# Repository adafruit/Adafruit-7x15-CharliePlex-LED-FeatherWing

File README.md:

## Adafruit 7x15 CharliePlex LED FeatherWings PCB
<a href="http://www.adafruit.com/products/3134"><br/>
Click here to purchase one from the Adafruit shop</a>

You wont be able to look away from the mesmerizing patterns created by this Adafruit 15x7 CharliePlex LED Matrix Display FeatherWing.  This 15x7 LED display can be paired with any of our Feather boards for a beautiful, bright grid of 105 charlieplexed LEDs. It even comes with a built-in charlieplex driver that is run over I2C.

We carry these FeatherWings in five vivid colors!

What is particularly nice about this Wing is the I2C LED driver chip has the ability to PWM each individual LED in a 15x7 grid so you can have beautiful LED lighting effects, without a lot of pin twiddling. Simply tell the chip which LED on the grid you want lit, and what brightness and it's all taken care of for you. You get 8-bit (256 level) dimming for each individual LED.

PCB files for 7x15 CharliePlex LED FeatherWings. The format is EagleCAD schematic and board layout

For more details, check out the product pages at

   * https://www.adafruit.com/product/3134
   * https://www.adafruit.com/product/3135
   * https://www.adafruit.com/product/3136
   * https://www.adafruit.com/product/3137
   * https://www.adafruit.com/product/3138

### License

Adafruit invests time and resources providing this open source design, please support Adafruit and open-source hardware by purchasing products from [Adafruit](https://www.adafruit.com)!

All text above must be included in any redistribution

Designed by Limor Fried/Ladyada for Adafruit Industries.
Creative Commons Attribution/Share-Alike, all text above must be included in any redistribution. 
See license.txt for additional information.

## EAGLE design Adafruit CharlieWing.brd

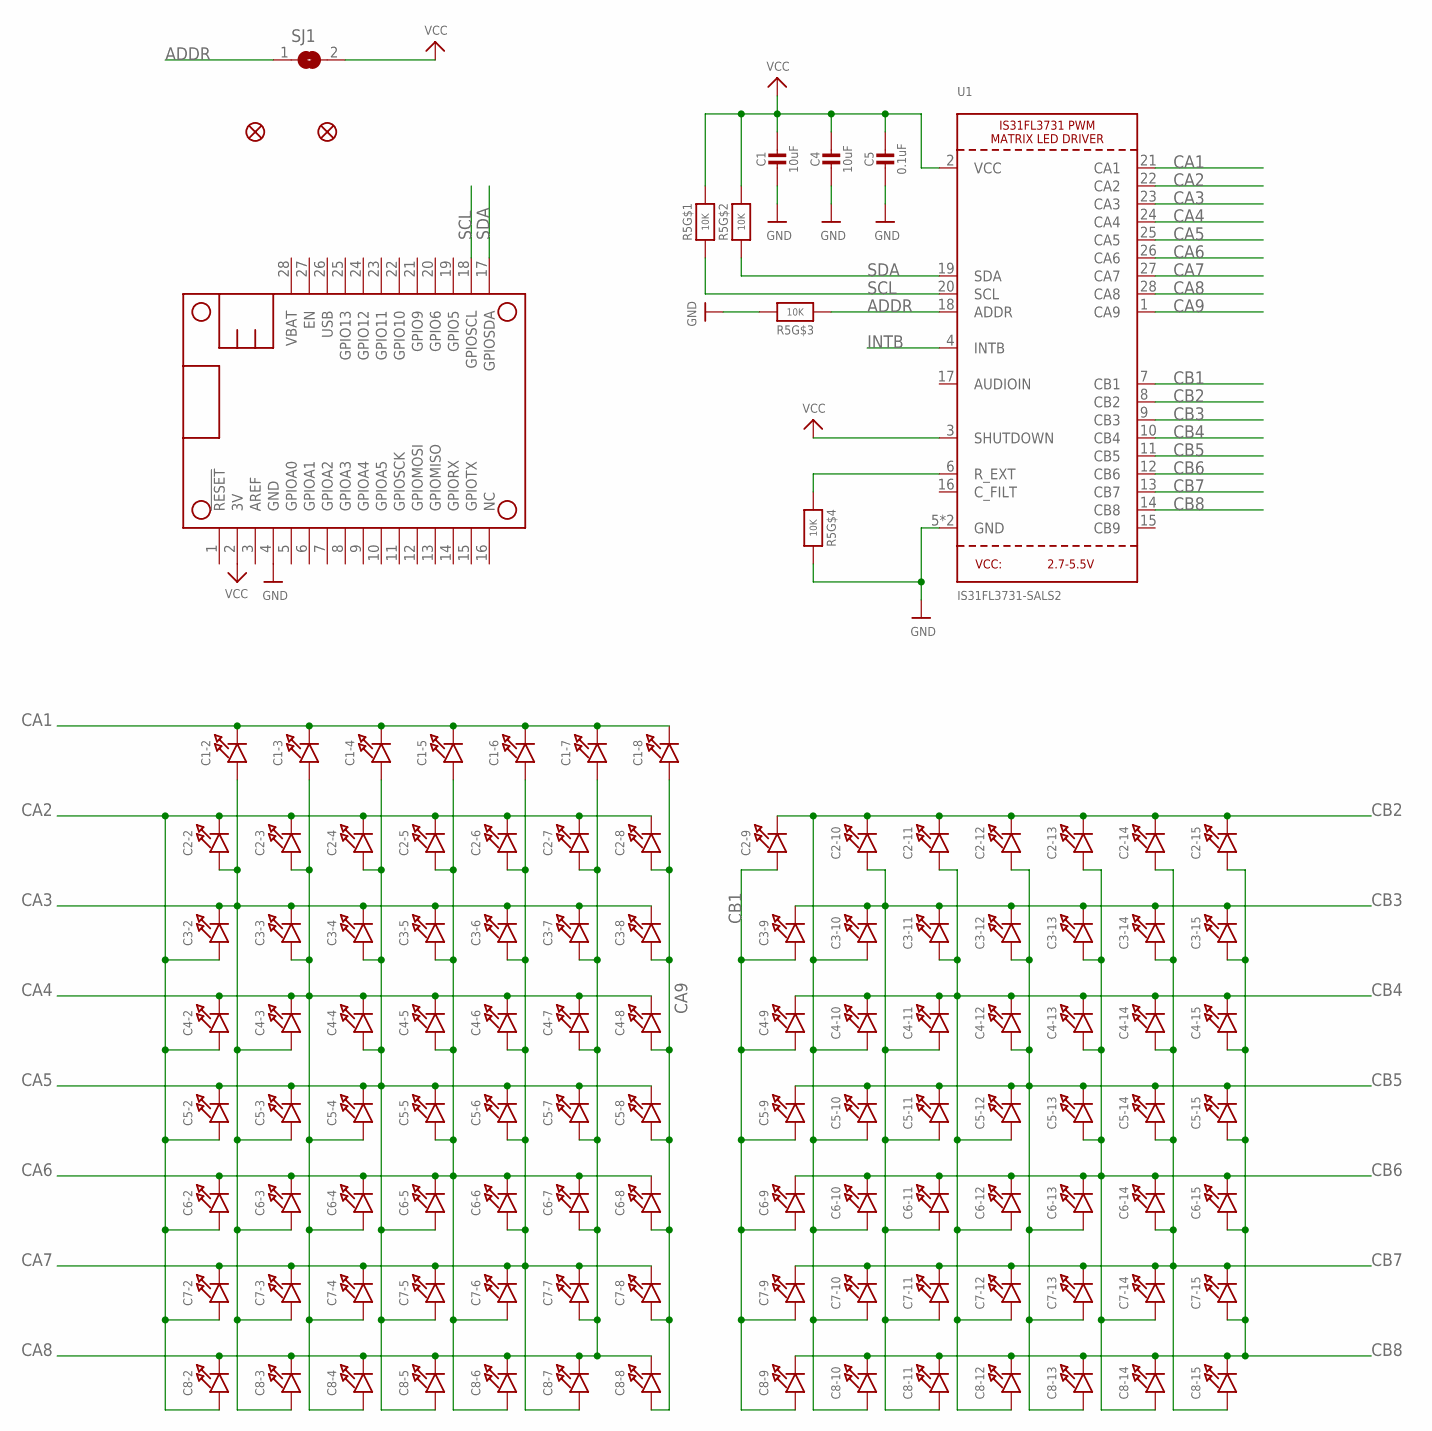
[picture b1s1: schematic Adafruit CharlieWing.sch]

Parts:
C1, C4: 10uF; 0805-NO
C1-2, C1-3, C1-4, C1-5, C1-6, C1-7, C1-8, C2-2, C2-3, C2-4, C2-5, C2-6, C2-7, C2-8, C2-9, C2-10, C2-11, C2-12, C2-13, C2-14, C2-15, C3-2, C3-3, C3-4, C3-5, C3-6, C3-7, C3-8, C3-9, C3-10, C3-11, C3-12, C3-13, C3-14, C3-15, C4-2, C4-3, C4-4, C4-5, C4-6, C4-7, C4-8, C4-9, C4-10, C4-11, C4-12, C4-13, C4-14, C4-15, C5-2, C5-3, C5-4, C5-5, C5-6, C5-7, C5-8, C5-9, C5-10, C5-11, C5-12, C5-13, C5-14, C5-15, C6-2, C6-3, C6-4, C6-5, C6-6, C6-7, C6-8, C6-9, C6-10, C6-11, C6-12, C6-13, C6-14, C6-15, C7-2, C7-3, C7-4, C7-5, C7-6, C7-7, C7-8, C7-9, C7-10, C7-11, C7-12, C7-13, C7-14, C7-15, C8-2, C8-3, C8-4, C8-5, C8-6, C8-7, C8-8, C8-9, C8-10, C8-11, C8-12, C8-13, C8-14, C8-15: LED0603_NOOUTLINE; CHIPLED_0603_NOOUTLINE
C5: 0.1uF; 0805-NO
FID1, FID2: FIDUCIAL""; FIDUCIAL_1MM
MS1: FEATHERWING
R5: 10K; RESPACK_4X0603
SJ1: SOLDERJUMPER; SOLDERJUMPER_ARROW_NOPASTE
U1: IS31FL3731-SALS2; QFN28_4MM_0.4MM

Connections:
ADDR: R5.3 (1), SJ1.1, U1.18 (ADDR)
CA1: C1-2.C, C1-3.C, C1-4.C, C1-5.C, C1-6.C, C1-7.C, C1-8.C, U1.21 (CA1)
CA2: C2-2.C, C2-3.C, C2-4.C, C2-5.C, C2-6.C, C2-7.C, C2-8.C, C3-2.A, C4-2.A, C5-2.A, C6-2.A, C7-2.A, C8-2.A, U1.22 (CA2)
CA3: C1-2.A, C2-2.A, C3-2.C, C3-3.C, C3-4.C, C3-5.C, C3-6.C, C3-7.C, C3-8.C, C4-3.A, C5-3.A, C6-3.A, C7-3.A, C8-3.A, U1.23 (CA3)
CA4: C1-3.A, C2-3.A, C3-3.A, C4-2.C, C4-3.C, C4-4.C, C4-5.C, C4-6.C, C4-7.C, C4-8.C, C5-4.A, C6-4.A, C7-4.A, C8-4.A, U1.24 (CA4)
CA5: C1-4.A, C2-4.A, C3-4.A, C4-4.A, C5-2.C, C5-3.C, C5-4.C, C5-5.C, C5-6.C, C5-7.C, C5-8.C, C6-5.A, C7-5.A, C8-5.A, U1.25 (CA5)
CA6: C1-5.A, C2-5.A, C3-5.A, C4-5.A, C5-5.A, C6-2.C, C6-3.C, C6-4.C, C6-5.C, C6-6.C, C6-7.C, C6-8.C, C7-6.A, C8-6.A, U1.26 (CA6)
CA7: C1-6.A, C2-6.A, C3-6.A, C4-6.A, C5-6.A, C6-6.A, C7-2.C, C7-3.C, C7-4.C, C7-5.C, C7-6.C, C7-7.C, C7-8.C, C8-7.A, U1.27 (CA7)
CA8: C1-7.A, C2-7.A, C3-7.A, C4-7.A, C5-7.A, C6-7.A, C7-7.A, C8-2.C, C8-3.C, C8-4.C, C8-5.C, C8-6.C, C8-7.C, C8-8.C, U1.28 (CA8)
CA9: C1-8.A, C2-8.A, C3-8.A, C4-8.A, C5-8.A, C6-8.A, C7-8.A, C8-8.A, U1.1 (CA9)
CB1: C2-9.A, C3-9.A, C4-9.A, C5-9.A, C6-9.A, C7-9.A, C8-9.A, U1.7 (CB1)
CB2: C2-9.C, C2-10.C, C2-11.C, C2-12.C, C2-13.C, C2-14.C, C2-15.C, C3-10.A, C4-10.A, C5-10.A, C6-10.A, C7-10.A, C8-10.A, U1.8 (CB2)
CB3: C2-10.A, C3-9.C, C3-10.C, C3-11.C, C3-12.C, C3-13.C, C3-14.C, C3-15.C, C4-11.A, C5-11.A, C6-11.A, C7-11.A, C8-11.A, U1.9 (CB3)
CB4: C2-11.A, C3-11.A, C4-9.C, C4-10.C, C4-11.C, C4-12.C, C4-13.C, C4-14.C, C4-15.C, C5-12.A, C6-12.A, C7-12.A, C8-12.A, U1.10 (CB4)
CB5: C2-12.A, C3-12.A, C4-12.A, C5-9.C, C5-10.C, C5-11.C, C5-12.C, C5-13.C, C5-14.C, C5-15.C, C6-13.A, C7-13.A, C8-13.A, U1.11 (CB5)
CB6: C2-13.A, C3-13.A, C4-13.A, C5-13.A, C6-9.C, C6-10.C, C6-11.C, C6-12.C, C6-13.C, C6-14.C, C6-15.C, C7-14.A, C8-14.A, U1.12 (CB6)
CB7: C2-14.A, C3-14.A, C4-14.A, C5-14.A, C6-14.A, C7-9.C, C7-10.C, C7-11.C, C7-12.C, C7-13.C, C7-14.C, C7-15.C, C8-15.A, U1.13 (CB7)
CB8: C2-15.A, C3-15.A, C4-15.A, C5-15.A, C6-15.A, C7-15.A, C8-9.C, C8-10.C, C8-11.C, C8-12.C, C8-13.C, C8-14.C, C8-15.C, U1.14 (CB8)
GND: C1.2, C4.2, C5.2, MS1.4 (GND), R5.5 (2), R5.6 (2), U1.5 (GND), U1.THERMAL (GND)
INTB: U1.4 (INTB)
R_EXT: R5.4 (1), U1.6 (R_EXT)
SCL: MS1.18 (GPIOSCL), R5.1, U1.20 (SCL)
SDA: MS1.17 (GPIOSDA), R5.2 (1), U1.19 (SDA)
VCC: C1.1, C4.1, C5.1, MS1.2 (3V), R5.7 (2), R5.8 (2), SJ1.2, U1.2 (VCC), U1.3 (SHUTDOWN)

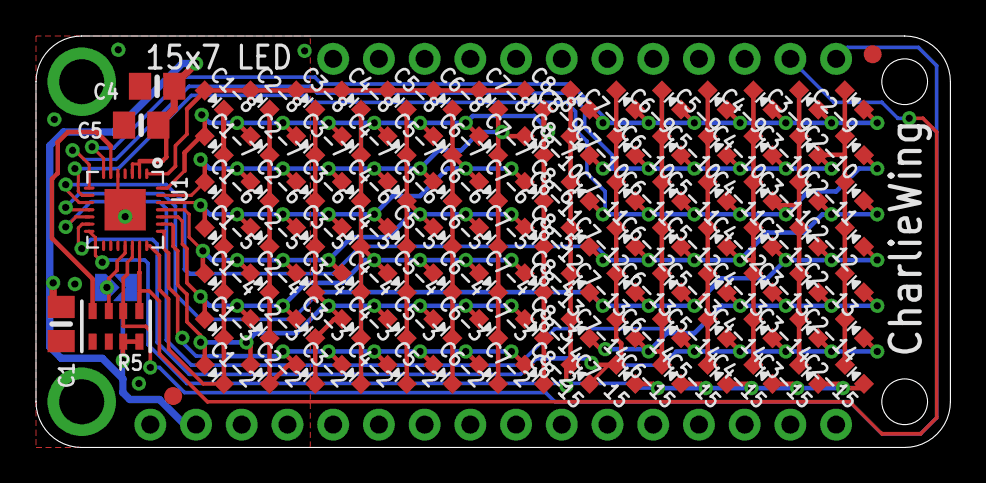
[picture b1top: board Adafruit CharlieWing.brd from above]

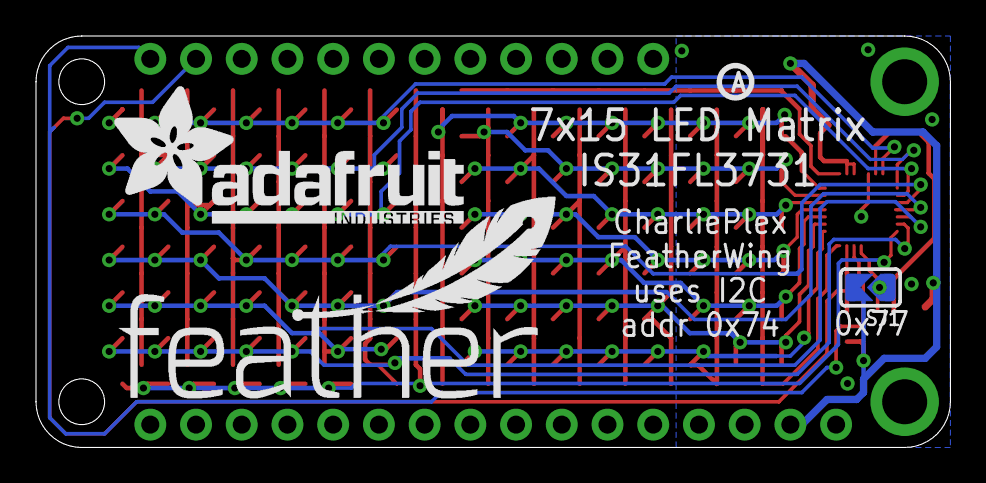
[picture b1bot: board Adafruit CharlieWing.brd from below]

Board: 2 copper layers, 50.8 x 22.9 mm, 117 parts (4 on the bottom side), 23 nets.

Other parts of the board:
U$1: PCBFEAT-REV-040
U$2: ADAFRUIT_TEXT_20MM
U$6: FEATHERLOGO

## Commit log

2016-05-20 release!

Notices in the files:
parts and their libraries:
microbuilder: This work is placed in the public domain, and may be freely used for commercial and non-commercial work with the following conditions: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
